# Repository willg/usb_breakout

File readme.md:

# USB Breakout

## Panelization
* In `usb_breakout_array.kicad_pcb` do the following:
* Append `usb_breakout.kicad_pcb`
* create array
    * Horizontal count: 1
    * Vertical count: 4
    * Vertical spacing: 25.5mm
    * Vertical offset: 0mm
* Add 3 lines between to `Eco1.User` where mouse bite tabs will be added
* run 
```
java -jar kicadutil.jar pcb
--file=array/usb_breakout_array.kicad_pcb panel --fillet=1
```
> uses [kicad-util](https://gitlab.com/dren.dk/kicad-util)

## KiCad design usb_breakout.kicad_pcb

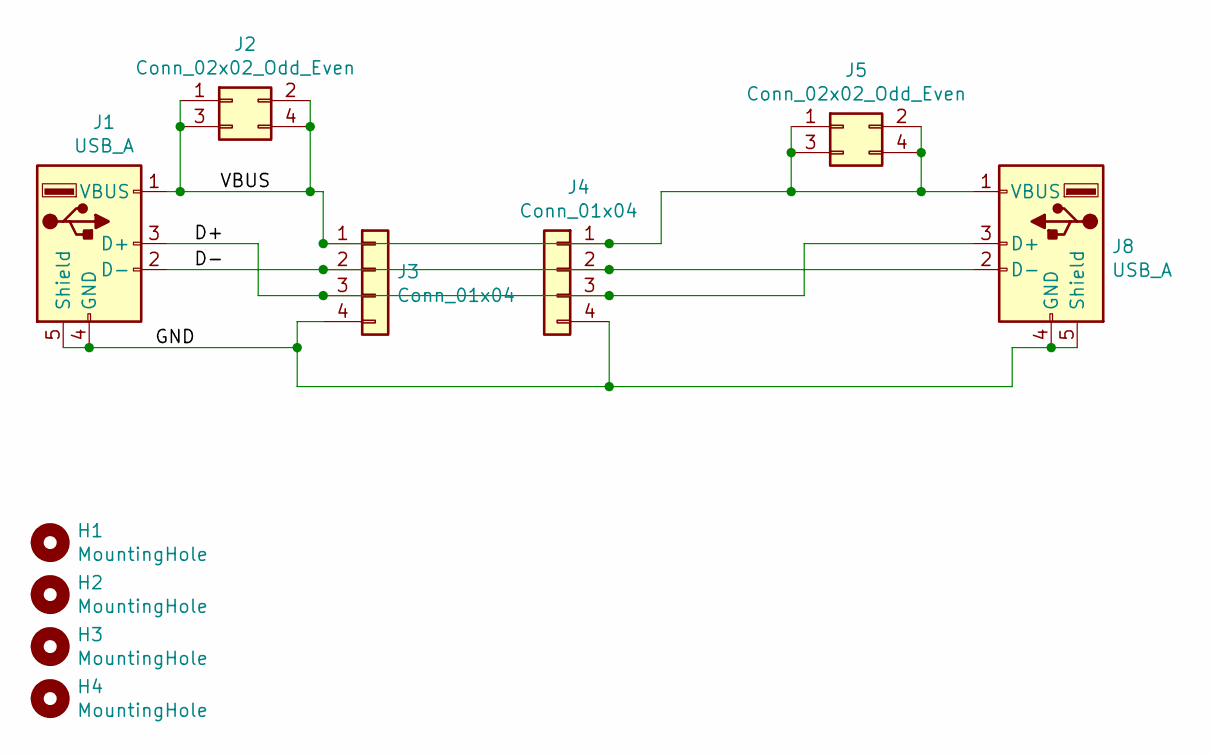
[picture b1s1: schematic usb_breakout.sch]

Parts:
H1, H2, H3, H4: MountingHole; MountingHole_4.3mm_M4
J1: USB_A; Molex_48037-2200_USB-A
J2, J5: Conn_02x02_Odd_Even; PinHeader_2x02_P2.54mm_Vertical
J3, J4: Conn_01x04; PinSocket_1x04_P2.54mm_Vertical
J8: USB_A; Amphenol_87583-2010RLF_USB-A-Female

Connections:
/D+: J1.3 (D+), J3.3, J4.3, J8.3 (D+)
/D-: J1.2 (D-), J3.2, J4.2, J8.2 (D-)
/GND: J1.4 (GND), J1.5 (Shield), J3.4, J4.4, J8.4 (GND), J8.5 (Shield)
/VBUS: J1.1 (VBUS), J2.1, J2.2, J2.3, J2.4, J3.1, J4.1, J5.1, J5.2, J5.3, J5.4, J8.1 (VBUS)

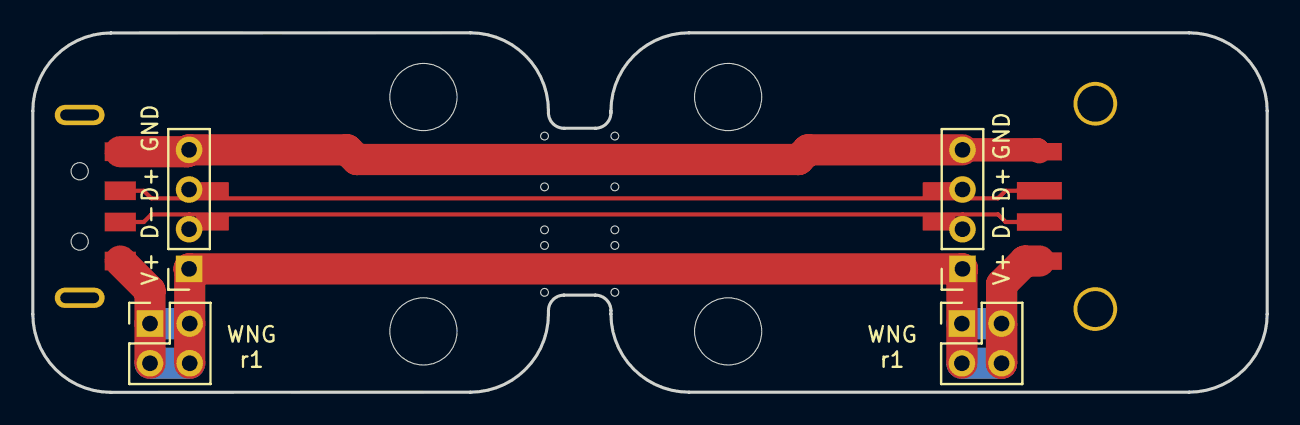
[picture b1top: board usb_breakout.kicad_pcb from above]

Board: 2 copper layers, 79.0 x 23.0 mm, 10 parts (0 on the bottom side), 4 nets.

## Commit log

2020-05-13 compacting layout
2020-05-13 added mouse bites, cleaned up board outline * board outline from fusion360 * added 0.5mm hole part for "mouse bites"
2020-05-16 prepare files to be fab'd * create readme with notes * create array * add mouse bites to array * generate gerbers
2020-05-22 add renders
